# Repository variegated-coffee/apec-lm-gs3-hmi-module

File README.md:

# LM GS3 HMI Module

*Front (the PCB's bottom side): the display bracket, the six buttons with two switches each, and the RGB LEDs between them. The display itself isn't modelled.*

*Back (the PCB's top side): the connectors, the LED and backlight drivers and the MCP23008. Both rendered in KiCad from the R1A design files.*

Espresso electronics are usually proprietary affairs with little to no expandability. The purpose of this project is to give everyone an open source alternative with lots of features and flexibility.

This board is the display and button module for the APEC carrier board for the La Marzocco GS3 (`apec-carrier-lm-gs3`), which is built around the [APEC SoM](https://github.com/variegated-coffee/apec-som). It carries a TFT display, six backlit buttons and their drivers, and connects to the carrier with a single cable. It's designed to fit into the original GS3 display module enclosure, replacing the display and button board in there.

This project isn't affiliated with or endorsed by La Marzocco. "La Marzocco" and "GS3" are used only to say which machine the module is designed for.

## High-level features

* 2.79" 142×428 IPS TFT display ([BuyDisplay](https://www.buydisplay.com/wide-angle-2-79-inch-142x428-color-ips-tft-display-nv3007-controller), NV3007 controller) on a 10-pin FFC connector (J2), driven over SPI
* Display backlight driver (U1, TI LM3410) set to about 76 mA, dimmable by PWM from the carrier
* Six buttons (Decrease, Increase, Select, Return, Function, Tea), matching the original buttons, each with two tactile switches (Omron B3FS-1050P in the BOM, or the cheaper E-Switch TL3301TF100QG), read through an MCP23008 I2C I/O expander (U2) with an interrupt line to the carrier
* Six RGB LEDs, one per button, driven by two TI LP5813 LED drivers (U4, U5) with built-in boost converters
* Header J4 for two external buttons and two external RGB LEDs, placed so that it is accessible using the original enclosure.
* Connects to the carrier with a 2×10 IDC ribbon cable (J13, the same pinout as the carrier's J13), which is what you'd use in a GS3, or an 18-pin EyeSPI FFC cable (J12), which is handier on the bench. It runs from the carrier's 3.3 V supply alone.
* Qwiic connector (J3) to extend the I2C bus
* A 3D-printed display bracket ([`GS3 TFT Shim.stl`](GS3%20TFT%20Shim.stl)) that holds the display in the right position

[ENGINEERING-NOTES.md](ENGINEERING-NOTES.md) has the details, [IO.md](IO.md) the signal and I2C assignments, and [MANUFACTURING-NOTES.md](MANUFACTURING-NOTES.md) how to build one.

## Project status

The current revision is R1A. It hasn't been manufactured yet; EV1 is the most recent revision that has been built. [CHANGELOG.md](CHANGELOG.md) lists what changed between them, including the changes firmware has to follow.

The firmware is developed separately.

## Safety

The module itself only uses 3.3 V from the carrier, but it is installed in an espresso machine, together with a carrier board that switches mains voltage, next to high-pressure hot water and steam. Read the carrier's safety warning before working on the machine, and never connect or disconnect the module while the machine is plugged in.

## Notice

This repository contains design files only. It is not a finished product, and it has not been tested or certified for compliance with any regulation, including but not limited to CE, UKCA or FCC requirements.

Anyone who manufactures, assembles, or places a product based on these files on the market does so as the manufacturer of that product, and is solely responsible for its safety, conformity assessment, marking, documentation, and any legal obligations that follow. If you build or use it yourself, you do so at your own risk.

The designs are provided “as is” under the CERN-OHL-P v2. See sections 5.1 and 5.2 for the disclaimer of warranty and limitation of liability.

## Opening the design

The project is made with KiCad 10. Every library the design needs is either in this repository or a KiCad standard library, so it opens without extra setup. A few parts exist only as copies embedded in the schematic and PCB, because their library files can't be redistributed. KiCad reports their libraries as missing, which is expected. See [THIRD_PARTY.md](THIRD_PARTY.md).

Vendor 3D models aren't included either. [3d-models/README.md](3d-models/README.md) lists where to download them for complete 3D views.

Parts of the schematic lie outside the A4 sheet frame. They are part of the design; zoom out to see them. A plot of the sheet (PDF or SVG) only shows what is inside the frame.

## License

The design files and documentation in this repository are licensed under the CERN Open Hardware Licence Version 2 – Permissive (CERN-OHL-P-2.0); see [LICENSE.txt](LICENSE.txt).

Some library files come from third parties and keep their own licences; see [THIRD_PARTY.md](THIRD_PARTY.md).

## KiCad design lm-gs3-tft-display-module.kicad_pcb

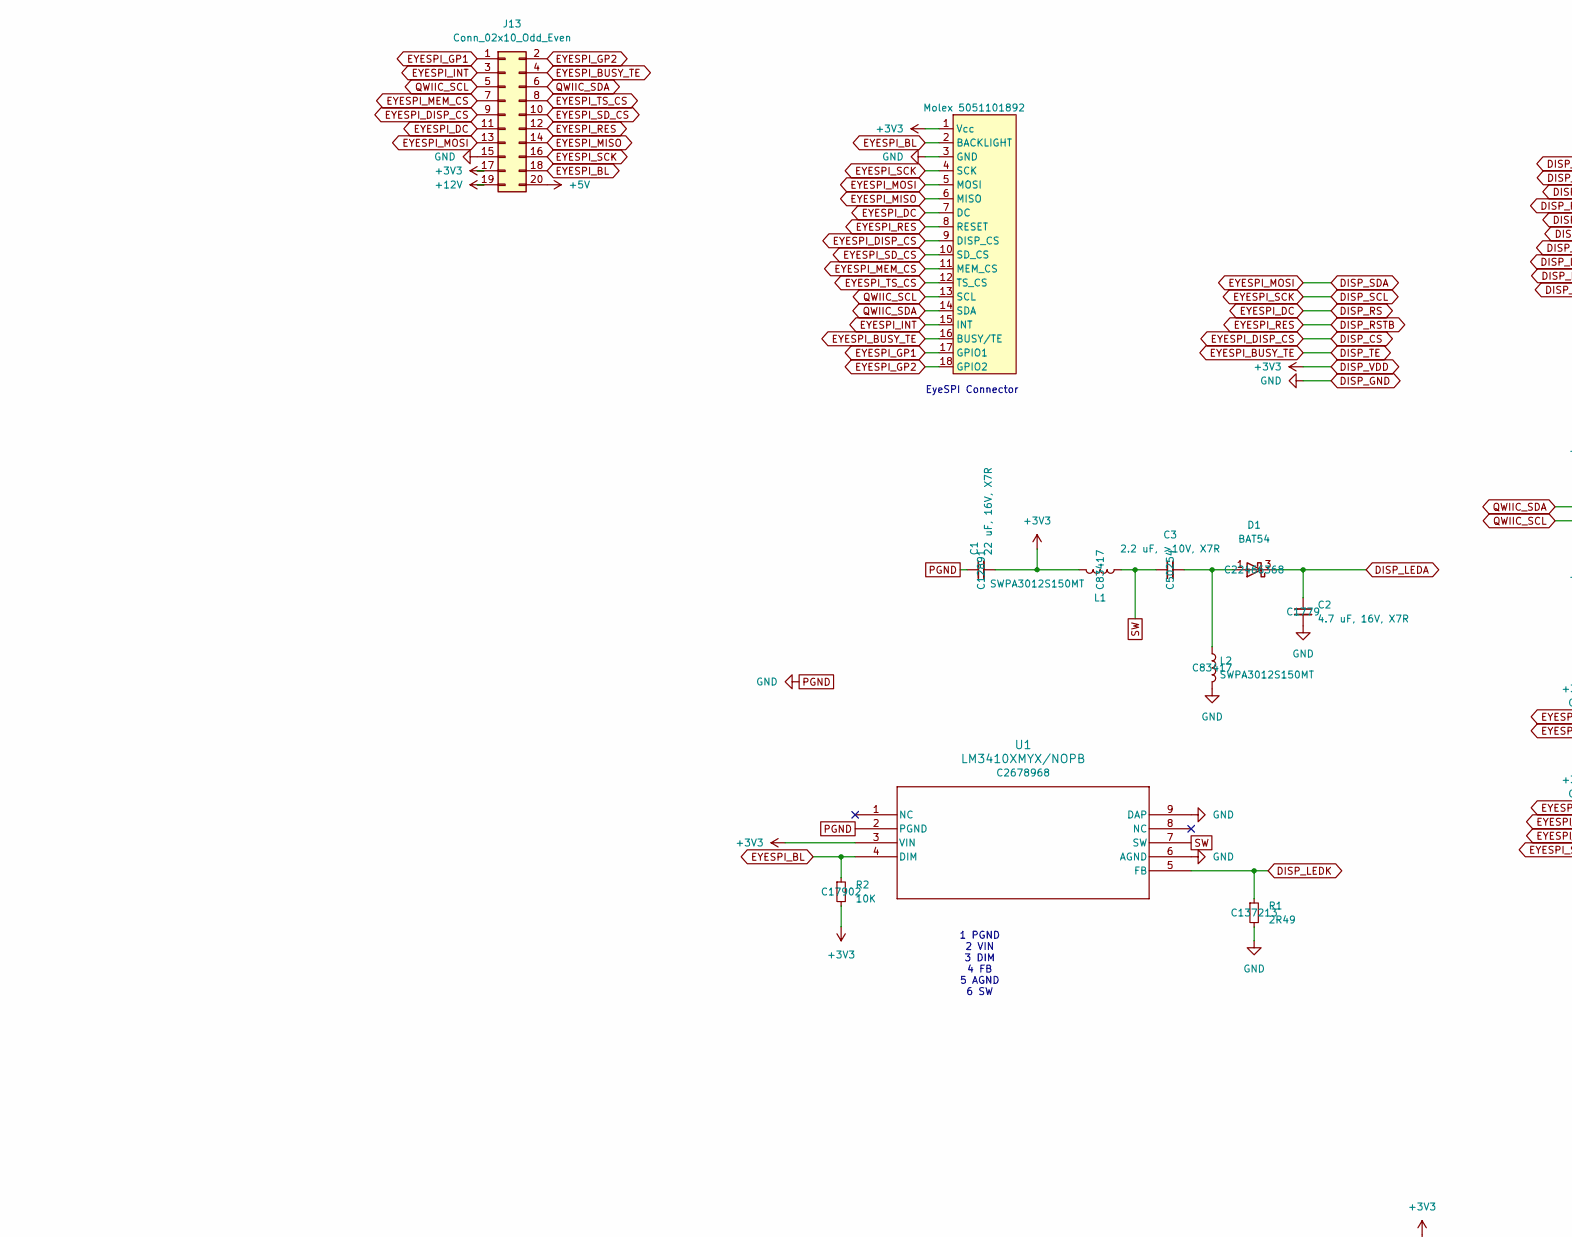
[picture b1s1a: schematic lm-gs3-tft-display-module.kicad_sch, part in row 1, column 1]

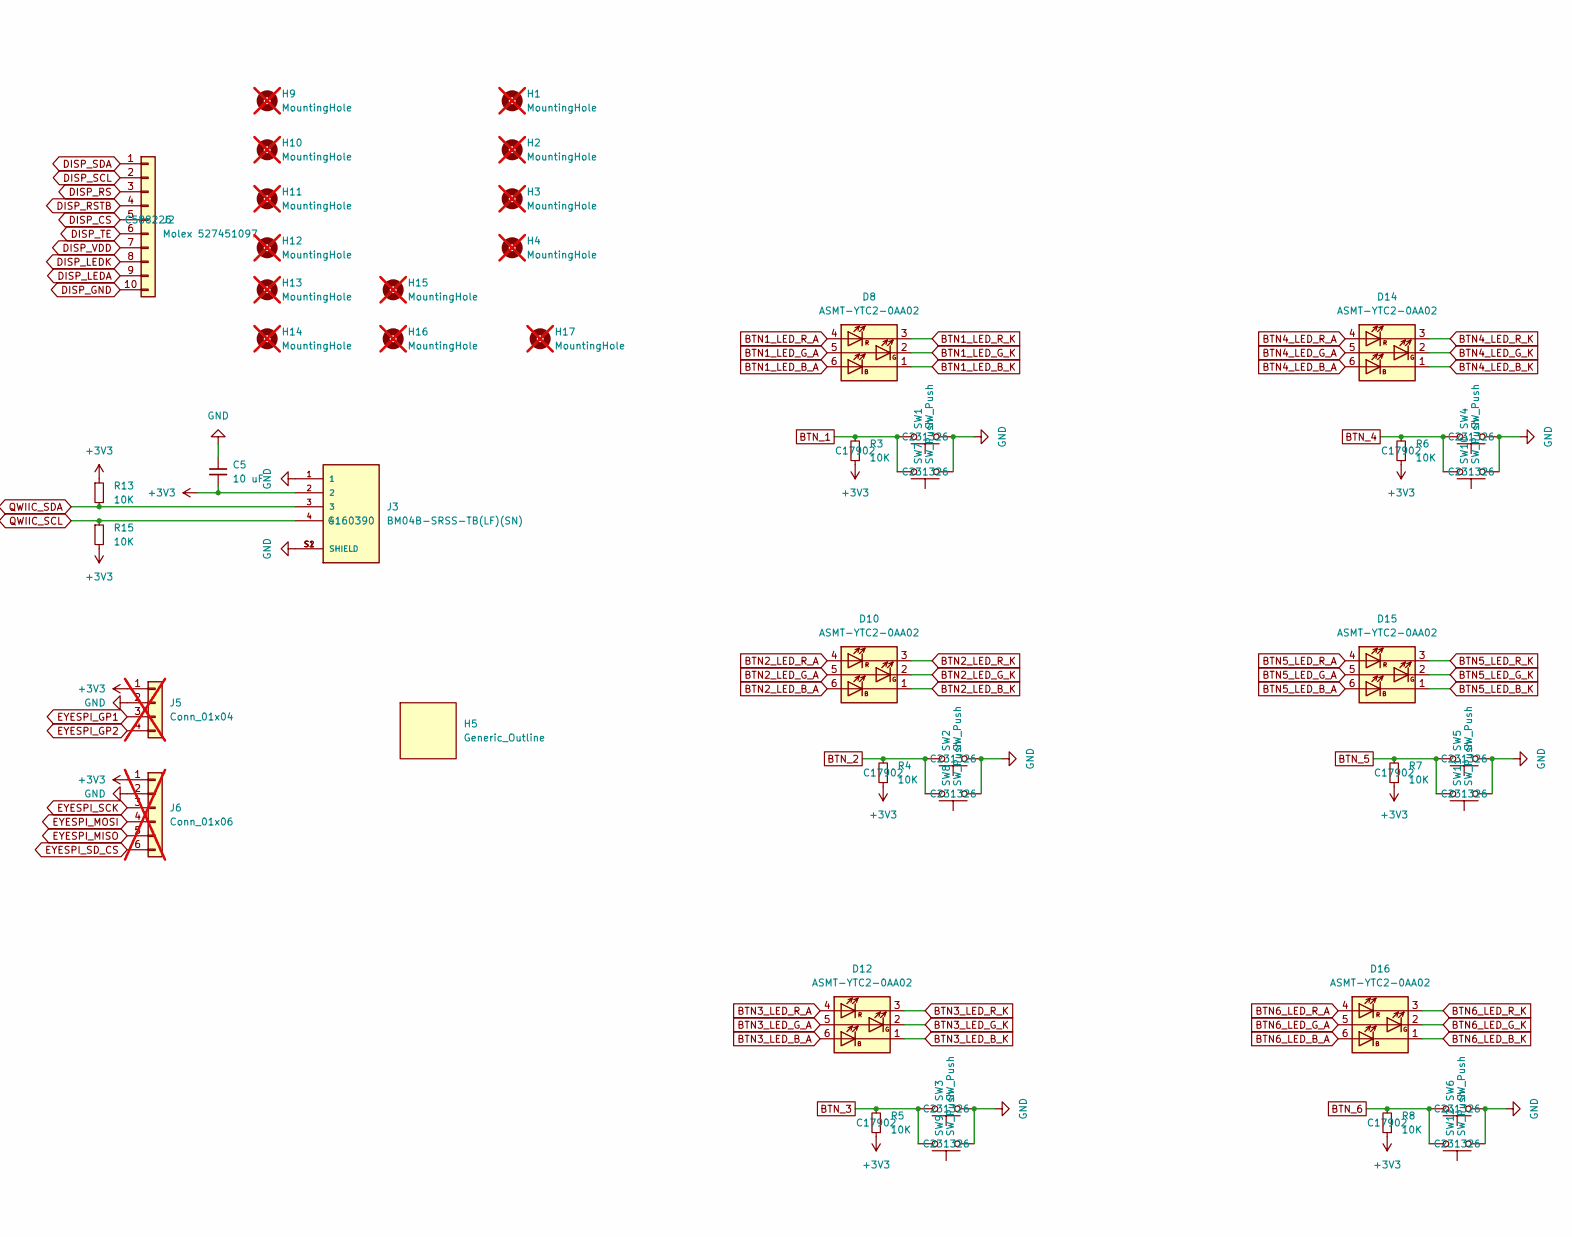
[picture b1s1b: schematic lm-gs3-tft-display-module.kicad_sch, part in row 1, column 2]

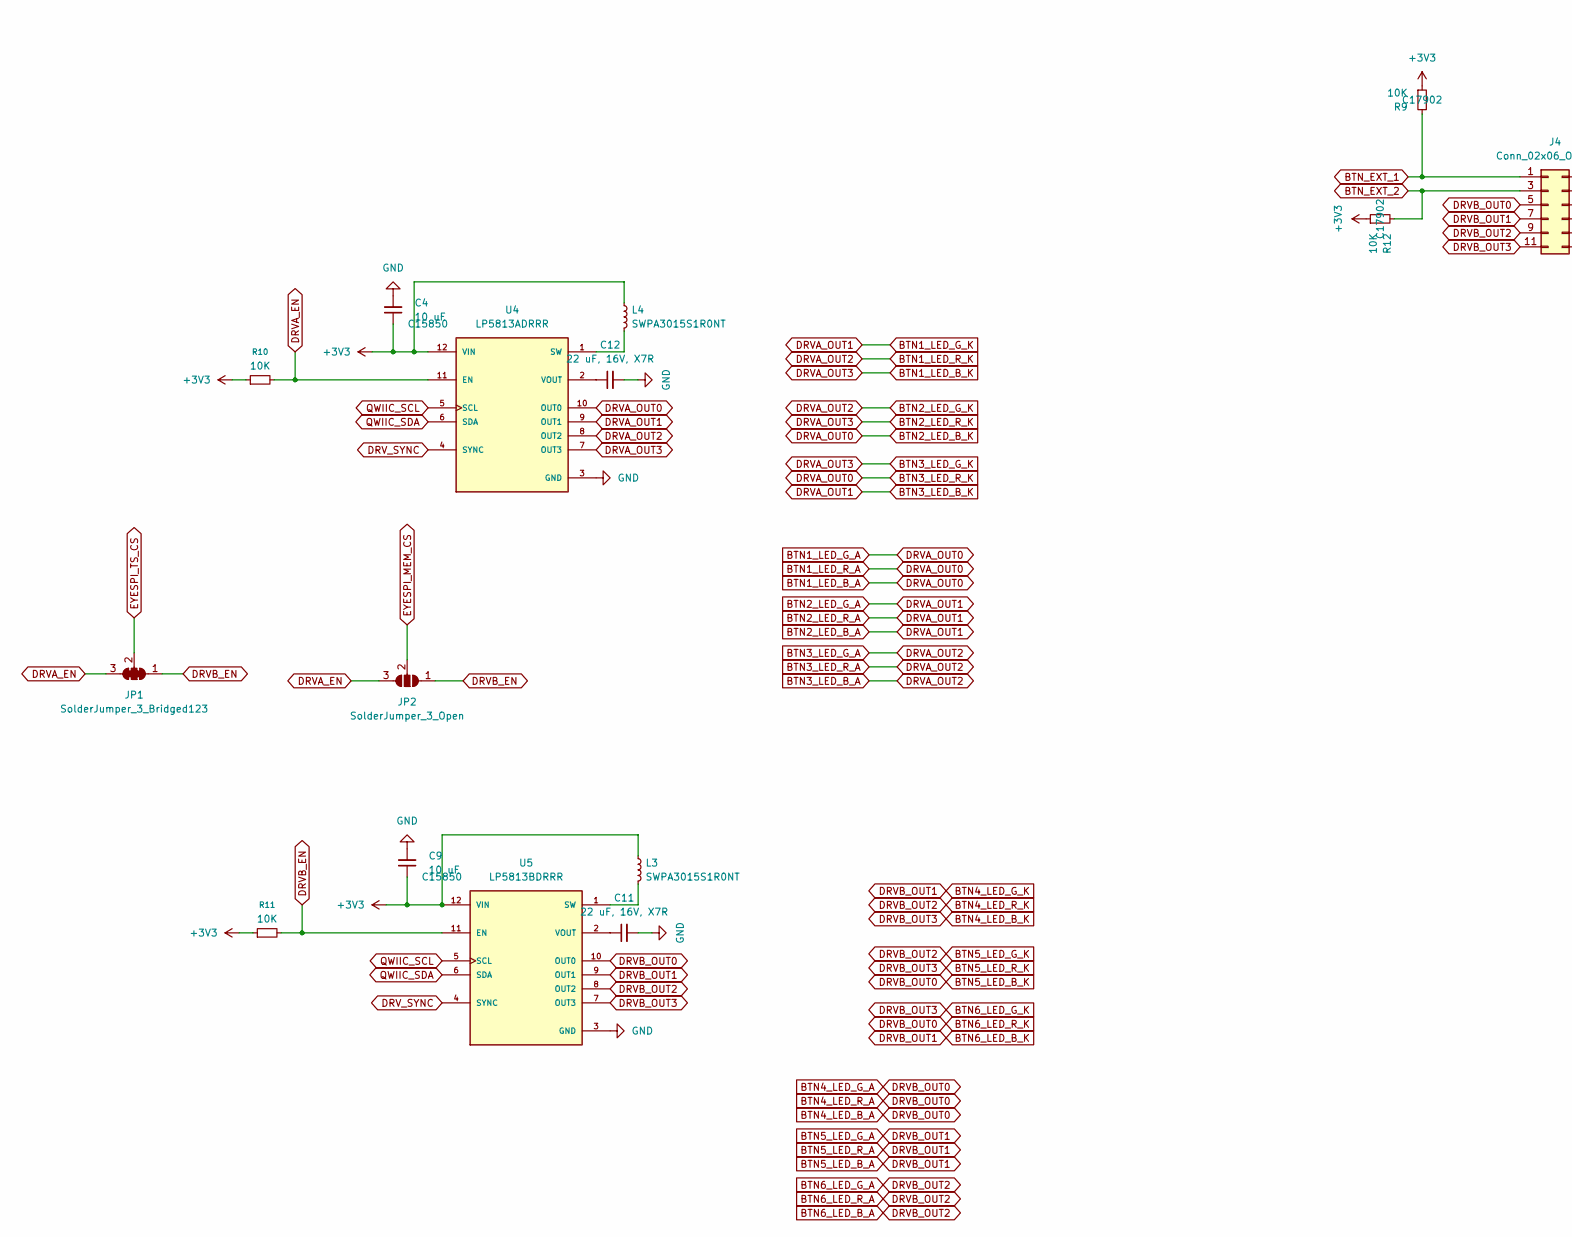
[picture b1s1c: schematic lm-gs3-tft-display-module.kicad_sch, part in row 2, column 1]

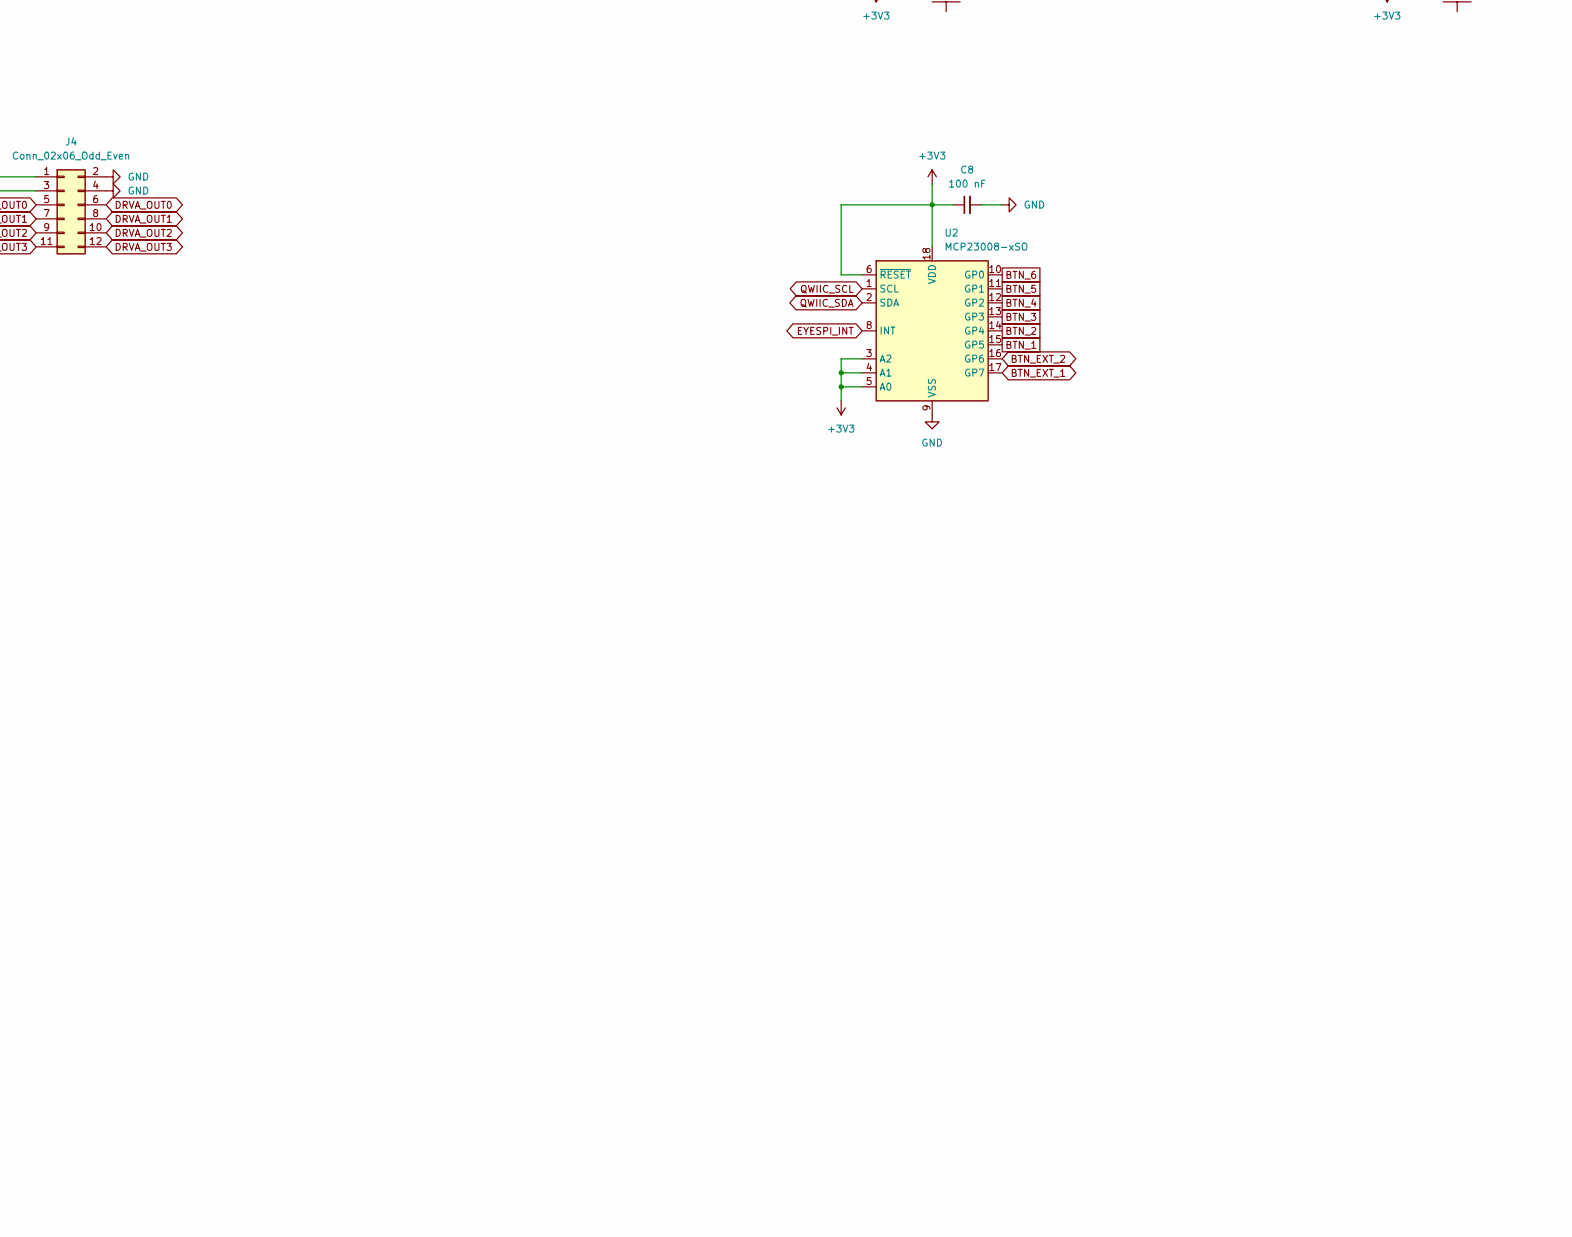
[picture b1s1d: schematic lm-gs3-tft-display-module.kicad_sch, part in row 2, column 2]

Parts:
C1, C11, C12: 22 uF, 16V, X7R; C_1206_3216Metric_Pad1.33x1.80mm_HandSolder; LCSC C12891
C2: 4.7 uF, 16V, X7R; C_0805_2012Metric_Pad1.18x1.45mm_HandSolder; LCSC C1779
C3: 2.2 uF, >10V, X7R; C_1206_3216Metric_Pad1.33x1.80mm_HandSolder; LCSC C50254
C4, C5, C9: 10 uF; C_0805_2012Metric_Pad1.18x1.45mm_HandSolder; LCSC C15850
C8: 100 nF; C_0805_2012Metric_Pad1.18x1.45mm_HandSolder; LCSC C28233
D1: BAT54; SOT-23; LCSC C22466368
D8, D10, D12, D14, D15, D16: ASMT-YTC2-0AA02; LED_Avago_PLCC6_3x2.8mm; LCSC C19531997
H1, H2, H3, H4, H9, H10: MountingHole; MountingHole_2.5mm; not fitted
H5: Generic_Outline; DisplayShim
H11, H12, H13, H14: MountingHole; MountingHole_3mm; not fitted
H15, H16, H17: MountingHole; MountingHole_4mm; not fitted
J2: Molex 527451097; CON_527451097_MOL; LCSC C588226
J3: BM04B-SRSS-TB(LF)(SN); JST_BM04B-SRSS-TB(LF)(SN); PARTREV N/A; LCSC C160390
J4: Conn_02x06_Odd_Even; IDC-Header_2x06_P2.54mm_Vertical_SMD; LCSC C22387746
J5: Conn_01x04; PinHeader_1x04_P2.54mm_Vertical; not fitted
J6: Conn_01x06; PinHeader_1x06_P2.54mm_Vertical; not fitted
J12: Molex 5051101892; CON_5051101892_MOL; LCSC C3036269
J13: Conn_02x10_Odd_Even; IDC-Header_2x10_P2.54mm_Vertical_SMD; LCSC C22387750
JP1: SolderJumper_3_Bridged123; SolderJumper-3_P1.3mm_Bridged123_Pad1.0x1.5mm
JP2: SolderJumper_3_Open; SolderJumper-3_P1.3mm_Open_Pad1.0x1.5mm
L1, L2: SWPA3012S150MT; L_Sunlord_SWPA3012S; LCSC C83417
L3, L4: SWPA3015S1R0NT; L_Sunlord_SWPA3015S; LCSC C43388
R1: 2R49; R_1206_3216Metric_Pad1.30x1.75mm_HandSolder; LCSC C137213
R2, R3, R4, R5, R6, R7, R8, R9, R10, R11, R12, R13, R15: 10K; R_1206_3216Metric_Pad1.30x1.75mm_HandSolder; LCSC C17902
SW1, SW2, SW3, SW4, SW5, SW6, SW7, SW8, SW9, SW10, SW11, SW12: SW_Push; SW_Flexible; LCSC C231326
U1: LM3410XMYX/NOPB; MUY08A; LCSC C2678968
U2: MCP23008-xSO; SOIC-18W_7.5x11.6mm_P1.27mm; LCSC C92253
U4: LP5813ADRRR; IC_LP5813ADRRR; PARTREV C; LCSC C31308275
U5: LP5813BDRRR; IC_LP5813ADRRR; PARTREV C; LCSC C31511637

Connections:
+5V: J13.20
+12V: J13.19
BTN1_LED_B_A: D8.4 (AR), D8.5 (AG), D8.6 (AB), D10.1 (KB), D12.3 (KR), J4.6, U4.10 (OUT0)
BTN1_LED_B_K: D8.1 (KB), D10.3 (KR), D12.2 (KG), J4.12, U4.7 (OUT3)
BTN1_LED_G_K: D8.2 (KG), D10.4 (AR), D10.5 (AG), D10.6 (AB), D12.1 (KB), J4.8, U4.9 (OUT1)
BTN1_LED_R_K: D8.3 (KR), D10.2 (KG), D12.4 (AR), D12.5 (AG), D12.6 (AB), J4.10, U4.8 (OUT2)
BTN4_LED_B_A: D14.4 (AR), D14.5 (AG), D14.6 (AB), D15.1 (KB), D16.3 (KR), J4.5, U5.10 (OUT0)
BTN4_LED_B_K: D14.1 (KB), D15.3 (KR), D16.2 (KG), J4.11, U5.7 (OUT3)
BTN4_LED_G_K: D14.2 (KG), D15.4 (AR), D15.5 (AG), D15.6 (AB), D16.1 (KB), J4.7, U5.9 (OUT1)
BTN4_LED_R_K: D14.3 (KR), D15.2 (KG), D16.4 (AR), D16.5 (AG), D16.6 (AB), J4.9, U5.8 (OUT2)
BTN_1: R3.2, SW1.2, SW7.2, U2.15 (GP5)
BTN_2: R4.2, SW2.2, SW8.2, U2.14 (GP4)
BTN_3: R5.2, SW3.2, SW9.2, U2.13 (GP3)
BTN_4: R6.2, SW4.2, SW10.2, U2.12 (GP2)
BTN_5: R7.2, SW5.2, SW11.2, U2.11 (GP1)
BTN_6: R8.2, SW6.2, SW12.2, U2.10 (GP0)
BTN_EXT_1: J4.1, R9.2, U2.17 (GP7)
BTN_EXT_2: J4.3, R12.2, U2.16 (GP6)
DISP_CS: J2.5, J12.9 (DISP_CS), J13.9
DISP_GND: C1.1, C2.2, C4.2, C5.1, C8.2, C9.2, C11.2, C12.2, J2.10, J3.1, J3.S1 (SHIELD), J3.S2 (SHIELD), J4.2, J4.4, J5.2, J6.2, J12.3 (GND), J13.15, L2.2, R1.2, SW1.1, SW2.1, SW3.1, SW4.1, SW5.1, SW6.1, SW7.1, SW8.1, SW9.1, SW10.1, SW11.1, SW12.1, U1.2 (PGND), U1.6 (AGND), U1.9 (DAP), U2.9 (VSS), U4.3 (GND), U4.13 (GND), U5.3 (GND), U5.13 (GND)
DISP_LEDA: C2.1, D1.3 (K), J2.9
DISP_LEDK: J2.8, R1.1, U1.5 (FB)
DISP_RS: J2.3, J12.7 (DC), J13.11
DISP_RSTB: J2.4, J12.8 (RESET), J13.12
DISP_SCL: J2.2, J6.3, J12.4 (SCK), J13.16
DISP_SDA: J2.1, J6.4, J12.5 (MOSI), J13.13
DISP_TE: J2.6, J12.16 (BUSY/TE), J13.4
DISP_VDD: C1.2, C4.1, C5.2, C8.1, C9.1, J2.7, J3.2, J5.1, J6.1, J12.1 (Vcc), J13.17, L1.2, L3.1, L4.1, R2.2, R3.1, R4.1, R5.1, R6.1, R7.1, R8.1, R9.1, R10.1, R11.1, R12.1, R13.1, R15.2, U1.3 (VIN), U2.3 (A2), U2.4 (A1), U2.5 (A0), U2.6 (~RESET), U2.18 (VDD), U4.12 (VIN), U5.12 (VIN)
DRVA_EN: JP1.3 (B), JP2.3 (B), R10.2, U4.11 (EN)
DRVB_EN: JP1.1 (A), JP2.1 (A), R11.2, U5.11 (EN)
DRV_SYNC: U4.4 (SYNC), U5.4 (SYNC)
EYESPI_BL: J12.2 (BACKLIGHT), J13.18, R2.1, U1.4 (DIM)
EYESPI_GP1: J5.3, J12.17 (GPIO1), J13.1
EYESPI_GP2: J5.4, J12.18 (GPIO2), J13.2
EYESPI_INT: J12.15 (INT), J13.3, U2.8 (INT)
EYESPI_MEM_CS: J12.11 (MEM_CS), J13.7, JP2.2 (C)
EYESPI_MISO: J6.5, J12.6 (MISO), J13.14
EYESPI_SD_CS: J6.6, J12.10 (SD_CS), J13.10
EYESPI_TS_CS: J12.12 (TS_CS), J13.8, JP1.2 (C)
unnamed: C3.2, D1.1 (A), L2.1
unnamed: L4.2, U4.1 (SW)
unnamed: C12.1, U4.2 (VOUT)
unnamed: L3.2, U5.1 (SW)
unnamed: C11.1, U5.2 (VOUT)
QWIIC_SCL: J3.4, J12.13 (SCL), J13.5, R15.1, U2.1 (SCL), U4.5 (SCL), U5.5 (SCL)
QWIIC_SDA: J3.3, J12.14 (SDA), J13.6, R13.2, U2.2 (SDA), U4.6 (SDA), U5.6 (SDA)
SW: C3.1, L1.1, U1.7 (SW)

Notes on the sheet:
1 PGND 2 VIN 3 DIM 4 FB 5 AGND 6 SW
EyeSPI Connector

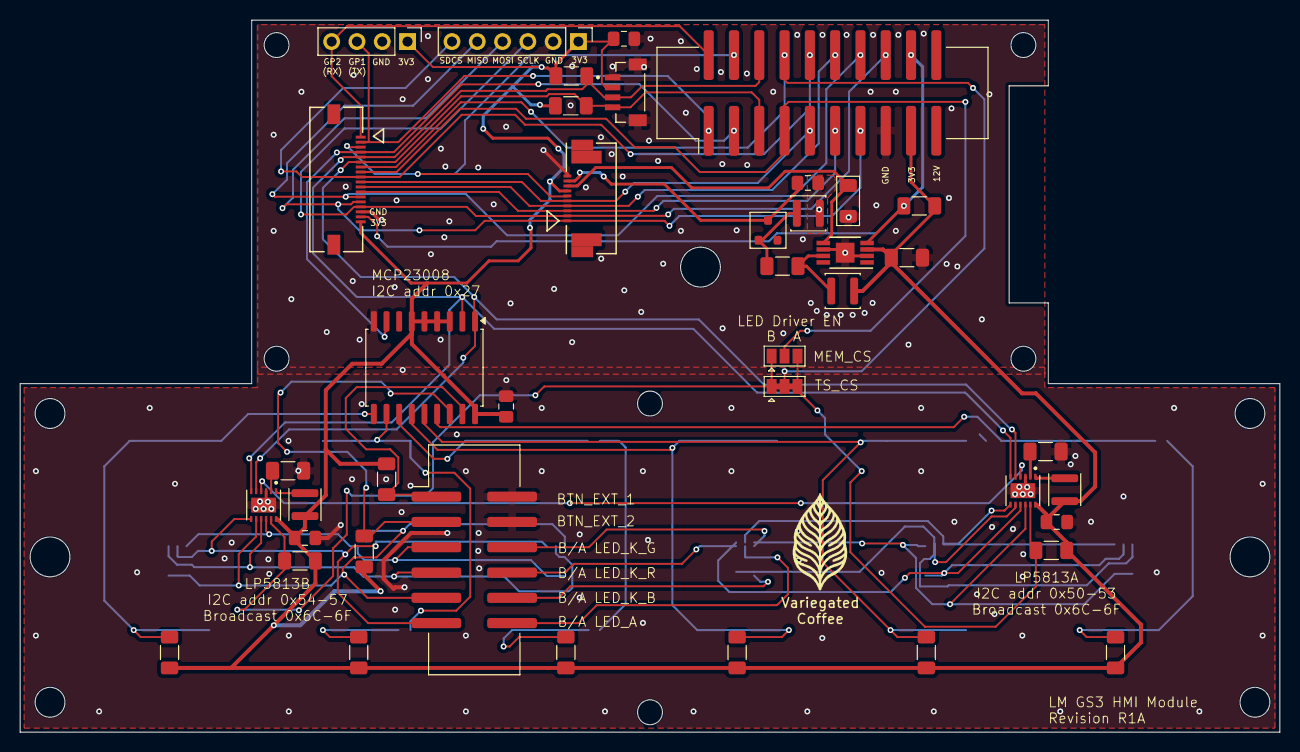
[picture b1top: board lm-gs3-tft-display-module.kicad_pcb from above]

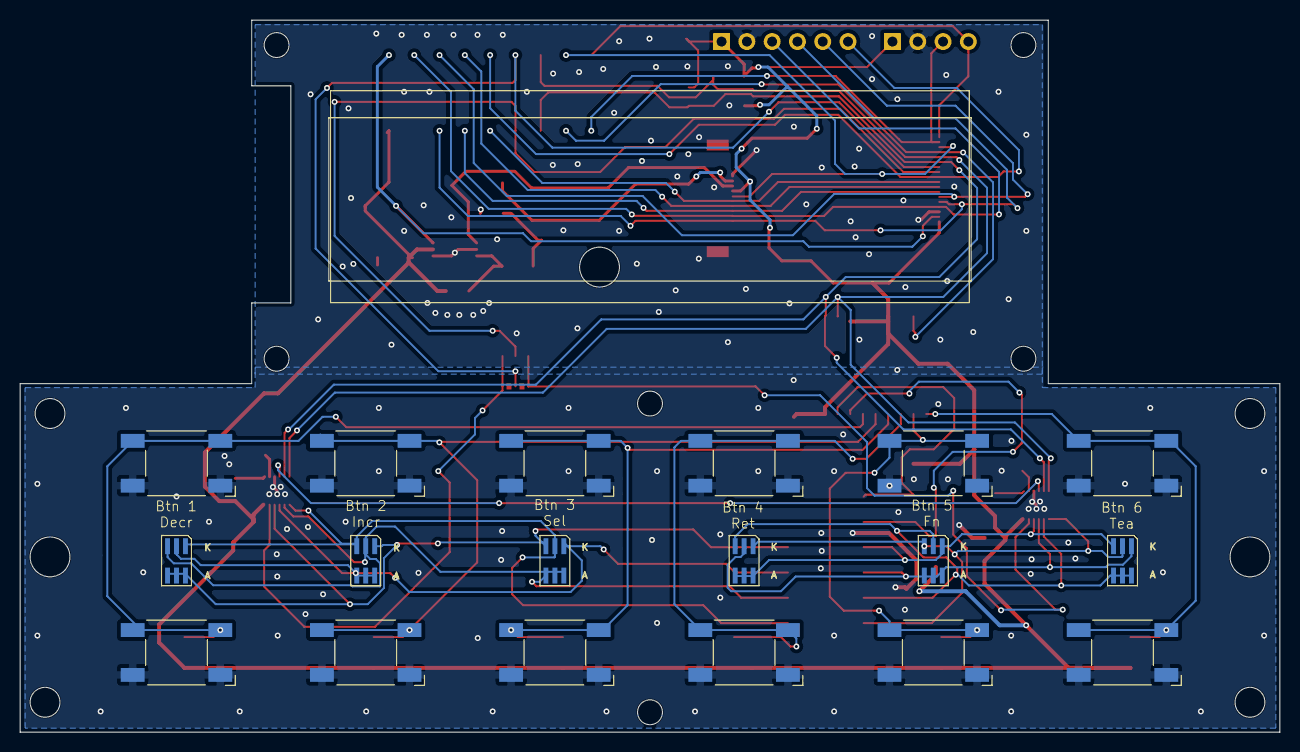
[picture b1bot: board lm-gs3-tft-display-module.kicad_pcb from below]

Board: 2 copper layers, 126.5 x 71.5 mm, 73 parts (19 on the bottom side), 45 nets.

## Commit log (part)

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2025-09-07 Initial import, as sent to manufacturer
